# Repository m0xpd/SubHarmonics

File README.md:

# SubHarmonics 

'SubHarmonics' is a Eurorack module which generates two squarewaves ('A' and 'B') which are sub-harmonics of another signal, 'X'.

The signal X is either  
i) generated by the module's internal Voltage Controlled Oscillator  
or  
ii) is derived from an external signal applied to the module's 'Ext X In' input.

The sub-harmonics are generated by hardware dividers, which divide the frequency of X by integer divisors (m, n) of 2, 4, 6, 8, 10, 12, 14, 16 or 18,
giving the unit a range of a little over four octaves (18 ≈ 2 <sup> 4.17 </sup> ). 

These divisors (m := f <sub> x </sub> / f <sub> A </sub>, n := f <sub> x </sub> / f <sub> B </sub>) are voltage controlled - they can be set by potentiometers or by control voltages applied from external sources.

It is seen that the signals A and B are themselves related in frequency by 'the ratio of two small integers' (m/n). So, in addition to each being 
sub-harmonics of X, the ratio between A and B often falls at a musically useful interval; 
<p align="center">
'SubHarmonics' generates harmony as well as bass.
</p>

Other applications of 'SubHarmonics' in Clock Division and Rhythm Generation are described [here.](https://github.com/m0xpd/SubHarmonics/blob/main/Applications/ClockDivision_and_RhythmGeneration.md)

### Internal Modulators

SubHarmonics includes a pair of internal modulators, which combine the A and B signals together (through an OR and an Exclusive OR operation) to
exploit and develop the harmonic relationship between A and B into a richer sound. The OR modulation is equivalent (for these signals A, B) to simple
amplitude modulation, as performed by (e.g.) an AND gate, whilst the Exclusive OR modulation implements the balanced modulation of A with B (as in a 
'ring modulator'). I described the equivalence of OR and AND gates as modulators for the special class of 'antipalindromic' inputs (such as the present 
A and B signals) at tedious length [here.](http://m0xpd.blogspot.com/2023/03/logic-gates-and-modulation-curiosity.html)

The two different modulation results are combined in a voltage-controlled crossfader circuit (controlled by a potentiometer or an external CV input) 
to give a single output which offers a choice OR A MIX of the modulation types at the 'Mod Mix' output.

An introductory video, demonstrating SubHarmonics' features, is available [here](https://youtu.be/j_IT1Ucp6_4)

### Setup

There are two presets that need adjustment on completion of the module to setup for use. Both are located on the topside of the Main Board.

TR2 (a multi-turn 1k preset) controls the 1V/Octave tracking. It should be set by connecting the module to a reliable source of pitch CV signals and monitoring the outputs. I use octave outputs from a BeatStep Pro (you can use a keyboard with CV pitch outputs or simply a known voltage source) and listen to the pitch change. I find it easy to tune octaves by ear but, if you are uncertain, use a tuner or frequency counter.

TR1 (a single turn 100k preset) controls the balance of the modulation mix crossfader. To set it properly requires access to an oscilloscope to see the 'Mod Mix' output waveform. If you have no access to a 'scope, set TR1 to about 60kΩ.

If you do have a 'scope, set the divisors to m=2, n=6 (using the front panel controls) and the frequency to an arbitrary value (around 300Hz). View the 'A' and 'Mod Mix' outputs on the 'scope. Adjust TR1 until you see these waveforms when you put the Mix control at extreme ends of its travel (or, equivalently, apply 0V or 5V CV signals to the Mix input):

(the yellow trace is the 'A' output, which stays the same in this setup process and is included only as a 'reference', the blue trace is the 'Mod Mix' output, which will change when you adjust TR1)  

[If you do not see this waveform on the ModMix output with these settings, it may be due to the phase relationship between the dividers - if this is the case, change the value of 'n' using the potentiometer all the way up to 18 and back to 6 and see if the phase is re-aligned. This is perfectly normal and is not a fault - there is another 'mode' of the system in the m=2, n=6 configuration to that illustrated above.]

Note that the 'Mod Mix' output is inverted (it runs 0 to approx -4V); there wasn't a spare op-amp stage to restore polarity after the crossfader. 
This doesn't matter in ordinary applications; the ear is insensitive to the inversion and it will sound the same! There are, however, some implications of this inversion which are important to the 'time-domain' applications discussed [here.](https://github.com/m0xpd/SubHarmonics/blob/main/Applications/ClockDivision_and_RhythmGeneration.md)

### Miscellaneous Details

The sub-harmonic generation and all signal processing is performed in hardware. 

A small (PIC) microcontroller is used to read the potentiometers and CV inputs and set the dividers. 

Details of the two PCBs and front panel are provided in the [Hardware](https://github.com/m0xpd/SubHarmonics/tree/main/Hardware) folder. Code for 
the 16F676 PIC is presented in the [Controller](https://github.com/m0xpd/SubHarmonics/tree/main/Controller) folder.

SubHarmonics is:  
12HP wide,   
requires 38mm behind the front panel (with the power header fitted) and  
draws 13.5mA from the 12V rail and 5mA from the -12V rail.  

The design is published under a Creative Commons CC BY-SA 4.0 [License](https://github.com/m0xpd/SubHarmonics/blob/main/LICENSE.txt).

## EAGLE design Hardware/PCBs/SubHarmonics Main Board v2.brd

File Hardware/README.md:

# Hardware
This folder contains hardware descriptions of the 'SubHarmonics' module.

The information is presented as EAGLE 'sch' and 'brd' files for the two PCBs (in the [PCBs folder](https://github.com/m0xpd/SubHarmonics/tree/main/Hardware/PCBs) ) and as a small Kicad project for the front panel (in
the FrontPanel folder).

SubHarmonics is implemented in two modules, each of which has its own PCB. There is a Main Board, hosting the majority of the electronics and
a Control Board, which contains all the front panel components including the division indicator LEDs and associated decoders.

## Main Board Description

The Main Board schematic is available [here](https://github.com/m0xpd/SubHarmonics/blob/main/Hardware/SubHarmonics%20Main%20Board%20Schematic%20v2.png) (or by clicking on the graphic below)

The VCO was inspired by the ['Shapes VCO' design by Moritz Klein](https://www.youtube.com/watch?v=QBatvo8bCa4), subsequently used in his VCO for the [Erica Synths Edu DIY VCO](https://www.ericasynths.lv/shop/diy-kits-1/edu-diy-vco/). Since developing 'SubHarmonics', I have learned that the core of the 40106 VCO was not a Klein original, but had been proposed earlier by Mark Shaner (a.k.a. "Synthmonger"), who published the idea [here](https://electro-music.com/forum/topic-28799.html) back in 2008.

The output of this 'Shaner' 40106 VCO - or the input from an external 'X' source - is applied to the 'Divider_In' input of the SubHarmonic Dividers, the input stages of which produce a 0 : 5V pulse at node 'X' on the schematic. There is a detailed description of the derivation of this pulse signal, including
discussion of options to set shared emitter resistor R19 to either maximise input sensitivity or enable a degree of noise immunity, [here.](https://github.com/m0xpd/SubHarmonics/blob/main/Hardware/Graphics/Input%20Stage%20Switching%20Behaviour.md) 

The system was designed around 'available materials' I found lying around my bench - in this case, mainly CD4000-series CMOS logic devices. 

The divisions in each of the two channels are achieved by a CD4015 (Decade counter) and a CD4051 (Analog Mux/Demux) in conventional 
configuration. The divisor is set by a PIC microcontroller, which reads a potentiometer or a CV input signal and decodes the voltage (0-5V) into 
one-of-8 settings for the dividers.

A further divide-by-2 stage, implemented in a CD4013 (D-type SR flip-flop) applied to the outputs of the dividers adds another octave of division 
(necessary to implement the m=2 setting on the A channel).

The outputs of the dividers, A and B (and their complements, not_A and not_B) are fed to two modulators, implemented in a quad NOR package (CD4001).

The results of the OR and XOR operations are mixed in a voltage-controlled crossfader, implemented in half an LM13700.

The [schematic](https://github.com/m0xpd/SubHarmonics/blob/main/Hardware/SubHarmonics%20Main%20Board%20Schematic%20v2.png) and [BoM](https://github.com/m0xpd/SubHarmonics/blob/main/Hardware/PCBs/SubHarmonics%20Main%20Board%20BoM%20v2.txt) show LM324 quad op-amps. These work fine in this application, but you can substitute the ubiquitous TL074 if you prefer. 

The Main Board includes an In-Circuit Serial Programming (ICSP) interface (JP1) to facilitate programming the PIC.

There is a [.sch](https://github.com/m0xpd/SubHarmonics/blob/main/Hardware/PCBs/SubHarmonics%20Main%20Board%20v2.sch) file, a [.brd](https://github.com/m0xpd/SubHarmonics/blob/main/Hardware/PCBs/SubHarmonics%20Main%20Board%20v2.brd) file and a [BoM](https://github.com/m0xpd/SubHarmonics/blob/main/Hardware/PCBs/SubHarmonics%20Main%20Board%20BoM%20v2.txt) for the Main Board in EAGLE format in the [PCBs folder](https://github.com/m0xpd/SubHarmonics/tree/main/Hardware/PCBs).

## Control Board Description

The Control Board schematic is available [here](https://github.com/m0xpd/SubHarmonics/blob/main/Hardware/Control%20Board%20Schematic.png) (or by clicking on the graphic below)

In addition to controls, inputs and outputs, the Control Board hosts the division indicator LEDs and decoders to control these (which again use 
CD4051 analog demuxers).

As well as to CV inputs for Pitch and FM, there are CV inputs for the divisors m and n and for the modulation mix. These last three are designed 
to operate over a range of 0 to 5V, but are protected such that voltages outside these limits will cause no damage.

A 0V input on the modulation mix CV input gives the XOR modulation and a 5V input gives the OR modulation (which is spectrally richer, as it includes the
harmonics of A and B as well as the sum and difference harmonics). An intermediate control voltage gives a mix of both modulation types.

There is a [.sch](https://github.com/m0xpd/SubHarmonics/blob/main/Hardware/PCBs/SubHarmonics%20Control%20Board%20v1.sch) file, a [.brd](https://github.com/m0xpd/SubHarmonics/blob/main/Hardware/PCBs/SubHarmonics%20Control%20Board%20v1.brd) file and a [BoM](https://github.com/m0xpd/SubHarmonics/blob/main/Hardware/PCBs/SubHarmonics%20Control%20Board%20v1%20BoM.txt) for the Control Board in EAGLE format in the [PCBs folder.](https://github.com/m0xpd/SubHarmonics/tree/main/Hardware/PCBs)

The Main and Control boards are joined by two 20-way 0.1 inch pitch headers. These have been specified with electrical redundancy (several pins are 
unused) to provide mechanical stability and security in assembling the module.

The completed PCBs are seen in the photo below, which shows the Main Board from both sides and the Control Board from the 'top' side (the front panel 
components all are mounted on the 'bottom' side).

## Front Panel

A simple Kicad project defining a Front Panel for the module is available in the [FrontPanel folder.](https://github.com/m0xpd/SubHarmonics/tree/main/Hardware/FrontPanel)

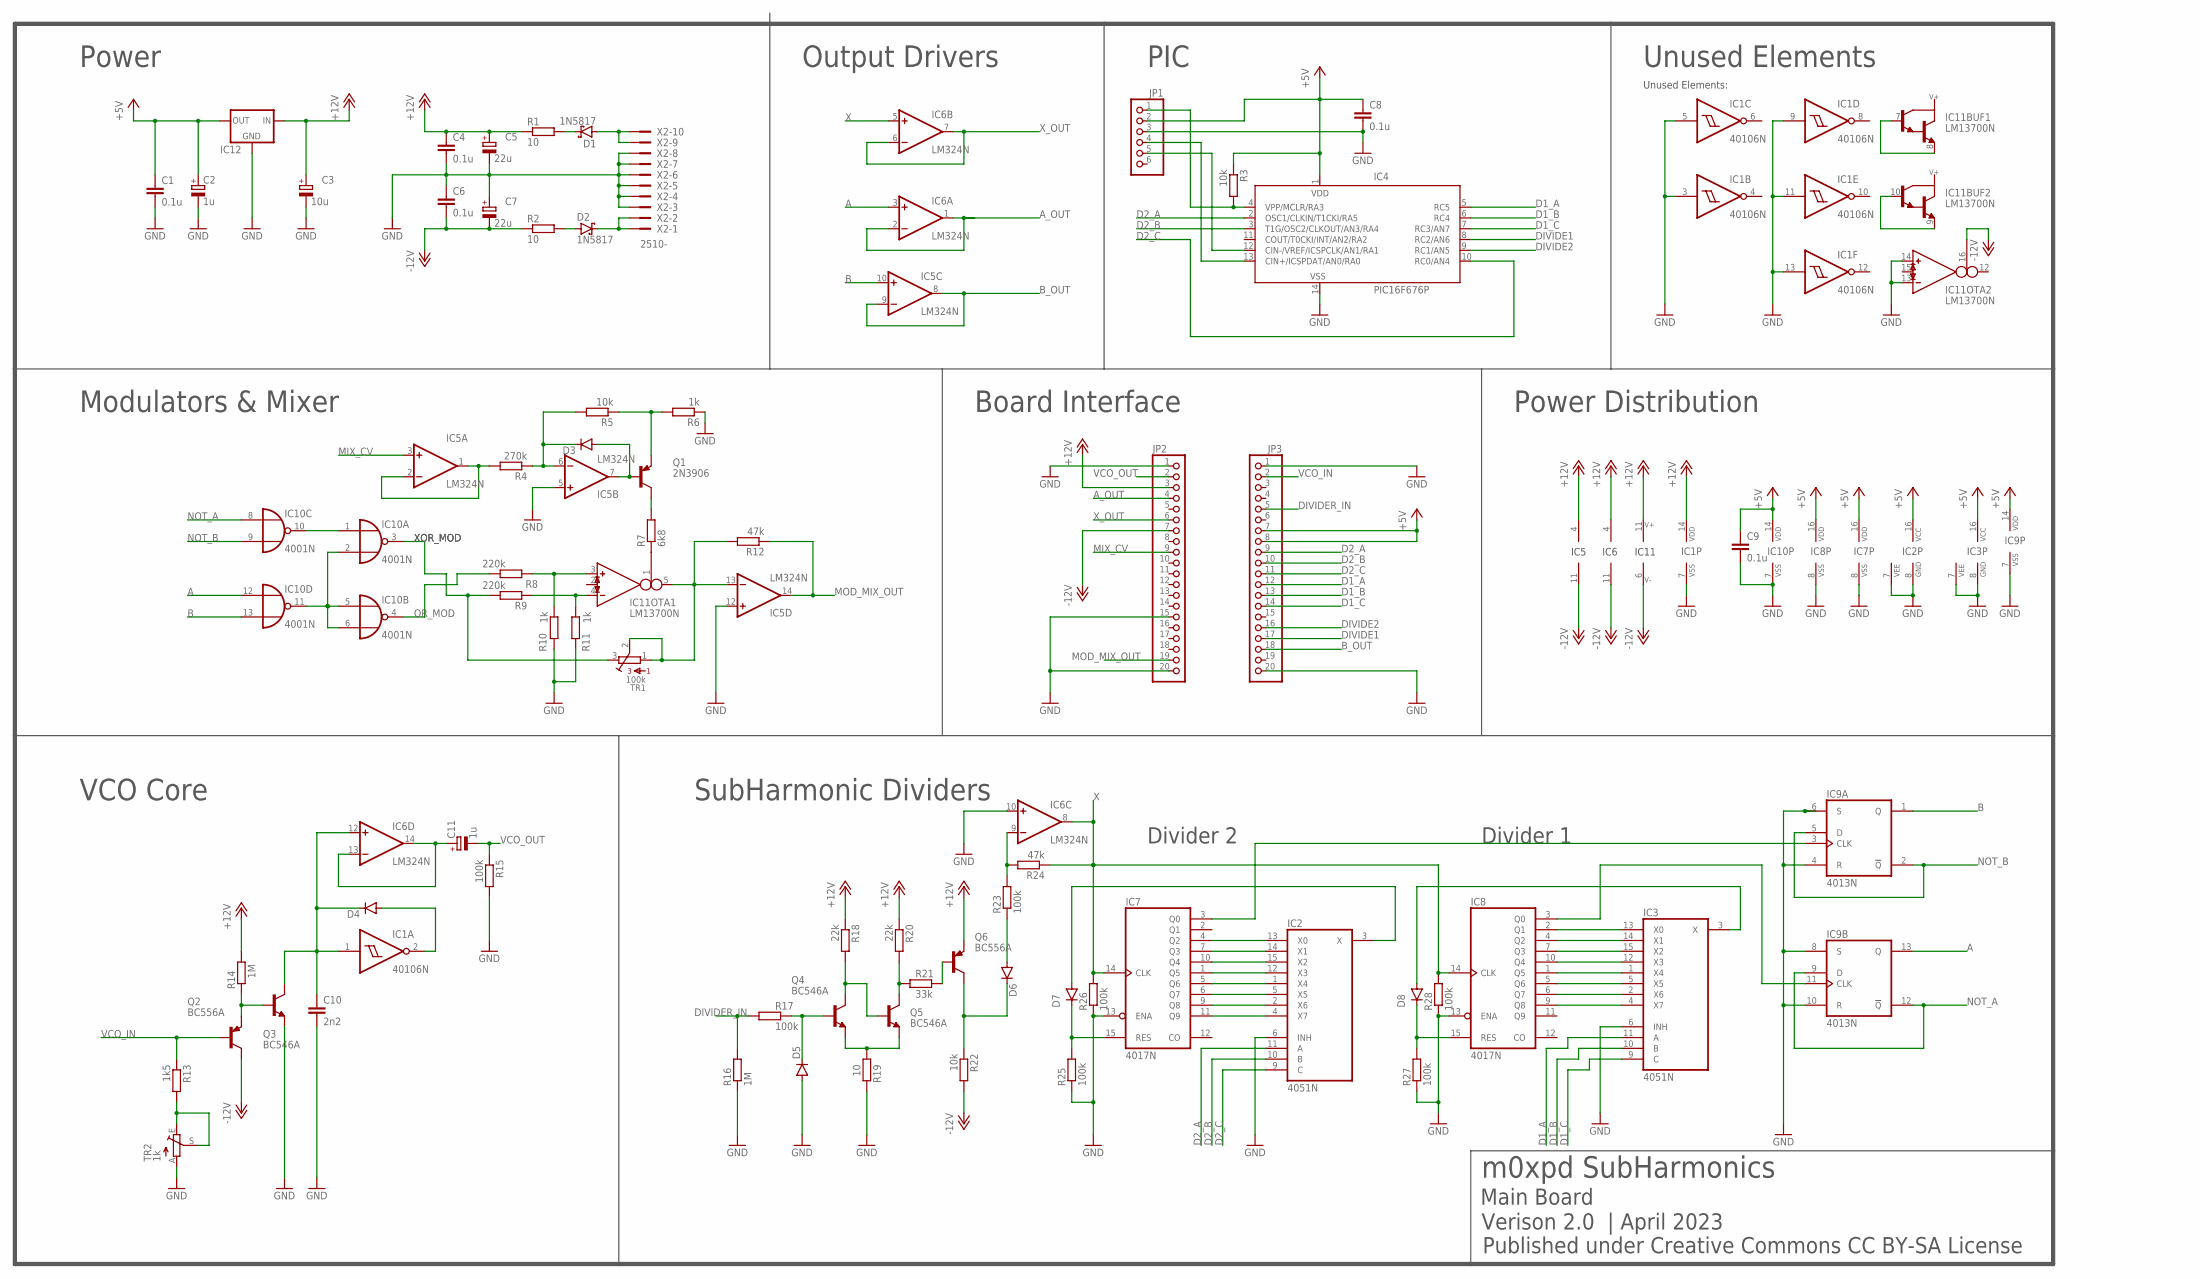
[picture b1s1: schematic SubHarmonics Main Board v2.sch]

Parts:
C1, C4, C6, C8, C9: 0.1u; C050-025X075
C2, C11: 1u; E2,5-5
C3: 10u; E2,5-5
C5, C7: 22u; E2,5-5
C10: 2n2; C050-030X075
D1, D2: 1N5817; DO35-7
D3, D4, D5, D6, D7, D8: 1N4148DO35-7; DO35-7
IC1: 40106N; DIL14
IC2, IC3: 4051N; DIL16
IC4: PIC16F676P; DIL14
IC5, IC6: LM324N; DIL14
IC7, IC8: 4017N; DIL16
IC9: 4013N; DIL14
IC10: 4001N; DIL14
IC11: LM13700N; DIL16
IC12: 78LXX
JP1: PINHD-1X6; 1X06
JP2, JP3: PINHD-1X20; 1X20
Q1: 2N3906; TO92
Q2, Q6: BC556A; TO92-EBC
Q3, Q4, Q5: BC546A; TO92-EBC
R1, R2, R19: 10; 0204/7
R3, R5, R22: 10k; 0204/7
R4: 270k; 0204/7
R6, R10, R11: 1k; 0204/7
R7: 6k8; 0204/7
R8, R9: 220k; 0204/7
R12, R24: 47k; 0204/7
R13: 1k5; 0204/7
R14, R16: 1M; 0204/7
R15, R17, R23, R25, R26, R27, R28: 100k; 0204/7
R18, R20: 22k; 0204/7
R21: 33k; 0204/7
TR1: 100k; BOURNS_3362P_TRIMMER
TR2: 1k; B64Y
X2: 2510-; PAK100/2500-10

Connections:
+5V: C1.1, C2.+, C8.1, C9.1, IC2.16 (VCC), IC3.16 (VCC), IC4.1 (VDD), IC7.16 (VDD), IC8.16 (VDD), IC9.14 (VDD), IC10.14 (VDD), IC12.OUT, JP1.2, JP3.7, JP3.8, R3.1
+12V: C3.+, C4.1, C5.+, IC1.14 (VDD), IC5.4 (V+), IC6.4 (V+), IC11.11 (V+), IC12.IN, JP2.3, Q6.E, R1.1, R14.2, R18.1, R20.1
-12V: C6.2, C7.-, IC5.11 (V-), IC6.11 (V-), IC11.6 (V-), IC11.16 (I_BIAS), JP2.7, Q2.C, R2.1, R22.2
A: IC6.3 (+IN), IC9.13 (Q), IC10.12 (I0)
A_OUT: IC6.1 (OUT), IC6.2 (-IN), JP2.4
B: IC5.10 (+IN), IC9.1 (Q), IC10.13 (I1)
B_OUT: IC5.8 (OUT), IC5.9 (-IN), JP3.18
D1_A: IC3.11 (A), IC4.5 (RC5), JP3.12
D1_B: IC3.10 (B), IC4.6 (RC4), JP3.13
D1_C: IC3.9 (C), IC4.7 (RC3/AN7), JP3.14
D2_A: IC2.11 (A), IC4.2 (OSC1/CLKIN/T1CKI/RA5), JP3.9
D2_B: IC2.10 (B), IC4.3 (T1G/OSC2/CLKOUT/AN3/RA4), JP3.10
D2_C: IC2.9 (C), IC4.10 (RC0/AN4), JP3.11
DIVIDE1: IC4.8 (RC2/AN6), JP3.17
DIVIDE2: IC4.9 (RC1/AN5), JP3.16
DIVIDER_IN: JP3.5, R16.2, R17.1
GND: C1.2, C2.-, C3.-, C4.2, C5.-, C6.1, C7.+, C8.2, C9.2, C10.2, D5.A, IC1.3 (I), IC1.5 (I), IC1.7 (VSS), IC1.9 (I), IC1.11 (I), IC1.13 (I), IC2.6 (INH), IC2.7 (VEE), IC2.8 (GND), IC3.6 (INH), IC3.7 (VEE), IC3.8 (GND), IC4.14 (VSS), IC5.5 (+IN), IC5.12 (+IN), IC6.10 (+IN), IC7.8 (VSS), IC7.13 (ENA), IC8.8 (VSS), IC8.13 (ENA), IC9.4 (R), IC9.6 (S), IC9.7 (VSS), IC9.8 (S), IC9.10 (R), IC10.7 (VSS), IC11.13 (IN_N), IC11.14 (IN_P), IC12.GND, JP1.3, JP2.1, JP2.15, JP2.20, JP3.1, JP3.20, Q3.E, R6.1, R10.2, R11.2, R15.2, R16.1, R19.2, R25.1, R26.1, R27.1, R28.1, TR2.A, X2.3, X2.4, X2.5, X2.6, X2.7, X2.8
MIX_CV: IC5.3 (+IN), JP2.9
MOD_MIX_OUT: IC5.14 (OUT), JP2.19, R12.1
unnamed: IC2.2 (X6), IC7.9 (Q8)
unnamed: IC5.1 (OUT), IC5.2 (-IN), R4.2
unnamed: D7.C, IC7.15 (RES), R25.2
unnamed: D7.A, IC2.3 (X)
unnamed: IC2.13 (X0), IC7.4 (Q2)
unnamed: IC2.14 (X1), IC7.7 (Q3)
unnamed: IC2.15 (X2), IC7.10 (Q4)
unnamed: IC2.12 (X3), IC7.1 (Q5)
unnamed: IC2.1 (X4), IC7.5 (Q6)
unnamed: IC2.5 (X5), IC7.6 (Q7)
unnamed: IC2.4 (X7), IC7.11 (Q9)
unnamed: IC11.3 (IN_P), R8.1, R10.1
unnamed: D1.A, X2.9, X2.10
unnamed: D1.C, R1.2
unnamed: IC4.4 (VPP/MCLR/RA3), JP1.1, R3.2
unnamed: D8.C, IC8.15 (RES), R27.2
unnamed: D8.A, IC3.3 (X)
unnamed: IC11.7 (B), IC11.8 (E)
unnamed: IC3.14 (X1), IC8.4 (Q2)
unnamed: IC3.15 (X2), IC8.7 (Q3)
unnamed: IC3.12 (X3), IC8.10 (Q4)
unnamed: IC3.1 (X4), IC8.1 (Q5)
unnamed: IC3.5 (X5), IC8.5 (Q6)
unnamed: IC3.2 (X6), IC8.6 (Q7)
unnamed: IC3.4 (X7), IC8.9 (Q8)
unnamed: IC11.4 (IN_N), R9.1, R11.1
unnamed: D2.A, R2.2
unnamed: D2.C, X2.1, X2.2
unnamed: IC11.9 (E), IC11.10 (B)
unnamed: IC11.1 (I_BIAS), R7.1
unnamed: IC4.13 (CIN+/ICSPDAT/AN0/RA0), JP1.4
unnamed: IC4.12 (CIN-/VREF/ICSPCLK/AN1/RA1), JP1.5
unnamed: IC3.13 (X0), IC8.2 (Q1)
unnamed: IC8.3 (Q0), IC9.11 (CLK)
unnamed: IC7.3 (Q0), IC9.3 (CLK)
unnamed: R13.2, TR2.E, TR2.S
unnamed: D6.C, Q6.C, R22.1
unnamed: D6.A, R23.1
unnamed: D4.A, IC1.2 (O)
unnamed: C10.1, D4.C, IC1.1 (I), IC6.12 (+IN), Q3.C
unnamed: Q2.E, Q3.B, R14.1
unnamed: IC6.9 (-IN), R23.2, R24.2
unnamed: C11.+, IC6.13 (-IN), IC6.14 (OUT)
unnamed: Q4.E, Q5.E, R19.1
unnamed: IC10.1 (I0), IC10.10 (O)
unnamed: IC10.2 (I1), IC10.5 (I0), IC10.6 (I1), IC10.11 (O)
unnamed: D5.C, Q4.B, R17.2
unnamed: Q1.1 (C), R7.2
unnamed: D3.C, IC5.6 (-IN), R4.1, R5.2
unnamed: Q4.C, Q5.B, R18.2
unnamed: Q5.C, R20.2, R21.1
unnamed: D3.A, IC5.7 (OUT), Q1.2 (B)
unnamed: Q1.3 (E), R5.1, R6.2
unnamed: Q6.B, R21.2
unnamed: IC5.13 (-IN), IC11.5 (OUT), R12.2, TR1.1, TR1.2
NOT_A: IC9.9 (D), IC9.12 (!Q), IC10.8 (I0)
NOT_B: IC9.2 (!Q), IC9.5 (D), IC10.9 (I1)
OR_MOD: IC10.4 (O), R8.2
VCO_IN: JP3.2, Q2.B, R13.1
VCO_OUT: C11.-, JP2.2, R15.1
X: IC6.5 (+IN), IC6.8 (OUT), IC7.14 (CLK), IC8.14 (CLK), R24.1, R26.2, R28.2
XOR_MOD: IC10.3 (O), R9.2, TR1.3
X_OUT: IC6.6 (-IN), IC6.7 (OUT), JP2.6

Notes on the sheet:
Unused Elements:
Divider 1
Divider 2
m0xpd SubHarmonics
Main Board
Verison 2.0 | April 2023
Published under Creative Commons CC BY-SA License
VCO Core
SubHarmonic Dividers
Modulators & Mixer
Power
Output Drivers
PIC
Unused Elements
Power Distribution
Board Interface
IC5
IC6
IC11

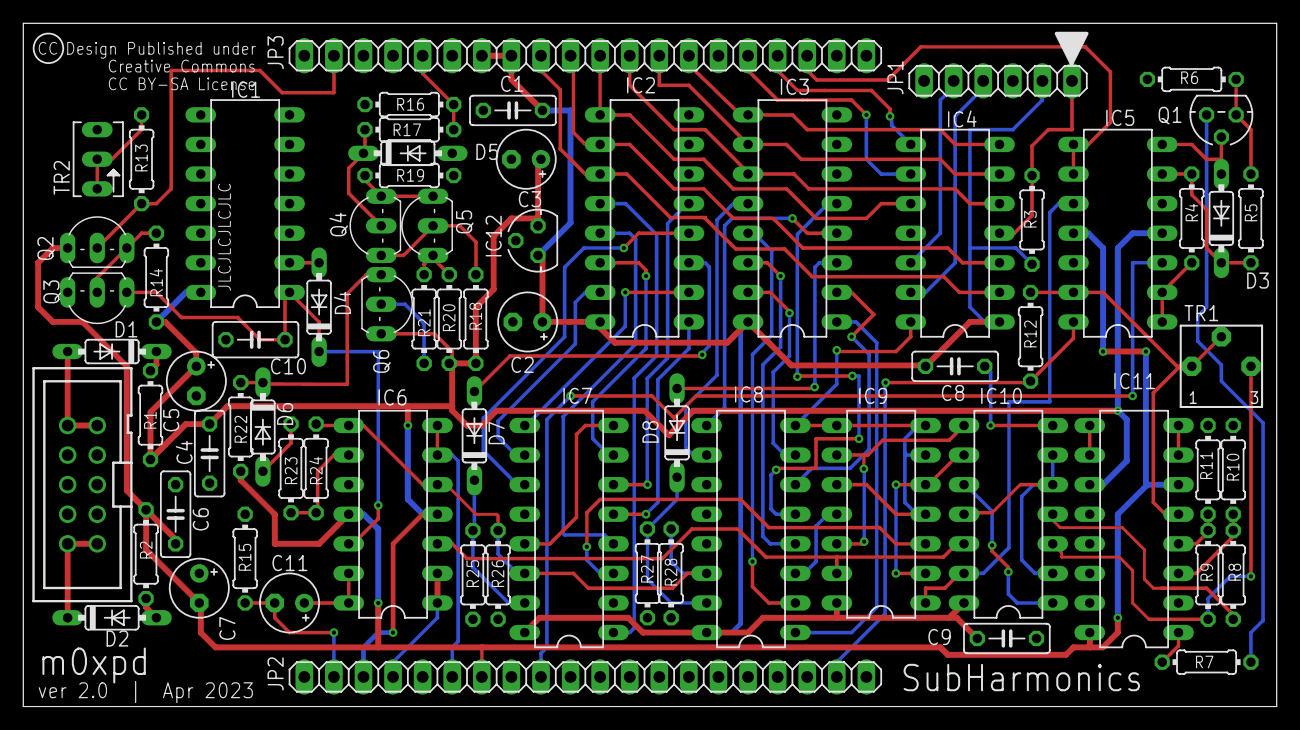
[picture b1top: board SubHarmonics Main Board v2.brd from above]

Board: 2 copper layers, 107.6 x 58.7 mm, 71 parts (0 on the bottom side), 82 nets.

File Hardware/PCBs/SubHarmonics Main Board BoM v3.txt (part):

Partlist exported from /Users/pauldarlington/Documents/EAGLE/projects/Harmonic Division Oscillator/SubHarmonics Main Board v3.sch at 22/10/2023 06:24

Part Value        Device                Package              Description                                    MF        MPN           OC_FARNELL OC_NEWARK POPULARITY SPICEPREFIX
C1   0.1u         C-EU050-025X075       C050-025X075         CAPACITOR, European symbol                                                                  29         C          
C2   1u           CPOL-EUE2.5-5         E2,5-5               POLARIZED CAPACITOR, European symbol                                                        16         C          
C3   10u          CPOL-EUE2.5-5         E2,5-5               POLARIZED CAPACITOR, European symbol                                                        16         C          
C4   0.1u         C-EU050-025X075       C050-025X075         CAPACITOR, European symbol                                                                  29         C          
C5   22u          CPOL-EUE2.5-5         E2,5-5               POLARIZED CAPACITOR, European symbol                                                        16         C          
C6   0.1u         C-EU050-025X075       C050-025X075         CAPACITOR, European symbol                                                                  29         C          
C7   22u          CPOL-EUE2.5-5         E2,5-5               POLARIZED CAPACITOR, European symbol                                                        16         C          
C8   0.1u         C-EU050-025X075       C050-025X075         CAPACITOR, European symbol                                                                  29         C          
C9   0.1u         C-EU050-025X075       C050-025X075         CAPACITOR, European symbol                                                                  29         C          
C10  2n2          C-EU050-030X075       C050-030X075         CAPACITOR, European symbol                                                                  9          C          
C11  1u           CPOL-EUE2.5-5         E2,5-5               POLARIZED CAPACITOR, European symbol                                                        16         C          
D1   1N5817       SCHOTTKY-DIODEDO35-7  DO35-7               Schottky Diode                                                                              3                     
D2   1N5817       SCHOTTKY-DIODEDO35-7  DO35-7               Schottky Diode                                                                              3                     
D3   1N4148DO35-7 1N4148DO35-7          DO35-7               DIODE                                                                                       58                    
D4   1N4148DO35-7 1N4148DO35-7          DO35-7               DIODE                                                                                       58                    
D5   1N4148DO35-7 1N4148DO35-7          DO35-7               DIODE                                                                                       58                    
D6   1N4148DO35-7 1N4148DO35-7          DO35-7               DIODE                                                                                       58                    
D7   1N4148DO35-7 1N4148DO35-7          DO35-7               DIODE                                                                                       58                    
D8   1N4148DO35-7 1N4148DO35-7          DO35-7               DIODE                                                                                       58                    
IC1  40106N       40106N                DIL14                Hex SCHMITT TRIGGER                                                                         4                     
IC2  4051N        4051N                 DIL16                8-channel ANALOG MULTIPLEXER                                                                15                    
IC3  4051N        4051N                 DIL16                8-channel ANALOG MULTIPLEXER                                                                15                    
IC4  PIC16F676P   PIC16F676P            DIL14                14-Pin, Flash-Based 8-Bit CMOS Microcontroller MICROCHIP PIC16F676-I/P 9760512    54K2829   0                     
IC5  LM324N       LM324N                DIL14                OP AMP                                                                                      9                     
IC6  LM324N       LM324N                DIL14                OP AMP                                                                                      9                     
IC7  4017N        4017N                 DIL16                COUNTER/DIVIDER                                                                             2                     
IC8  4017N        4017N                 DIL16                COUNTER/DIVIDER                                                                             2                     
IC9  4013N        4013N                 DIL14                Dual D FLIP FLOP, set/reset                                                                 4                     
IC10 4001N        4001N                 DIL14                Quad 2-input NOR                                                                            1                     
IC11 LM13700N     LM13700N              DIL16                Dual OTA with buffers                                                                                             
IC12              78LXX                 78LXX                VOLTAGE REGULATOR                                                                           6                     
JP1               PINHD-1X6             1X06                 PIN HEADER                                                                                  79                    
JP2               PINHD-1X20            1X20                 PIN HEADER                                                                                  6                     
JP3               PINHD-1X20            1X20                 PIN HEADER                                                                                  6                     
Q1   2N3906       2N3906                TO92                 PNP Transistor                                                                              11                    
Q2   BC556A       BC556A                TO92-EBC             PNP Transistror                                                                             0                     
Q3   BC546A       BC546A                TO92-EBC             NPN Transistor                                                                              0                     
Q4   BC546A       BC546A                TO92-EBC             NPN Transistor                                                                              0                     
Q5   BC546A       BC546A                TO92-EBC             NPN Transistor                                                                              0                     
Q6   BC556A       BC556                 TO92-EBC             PNP Transistror                                                                             2                     
R1   10           R-EU_0204/7           0204/7               RESISTOR, European symbol                                                                   79         R          
R2   10           R-EU_0204/7           0204/7               RESISTOR, European symbol                                                                   79         R          
R3   10k          R-EU_0204/7           0204/7               RESISTOR, European symbol                                                                   79         R          
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
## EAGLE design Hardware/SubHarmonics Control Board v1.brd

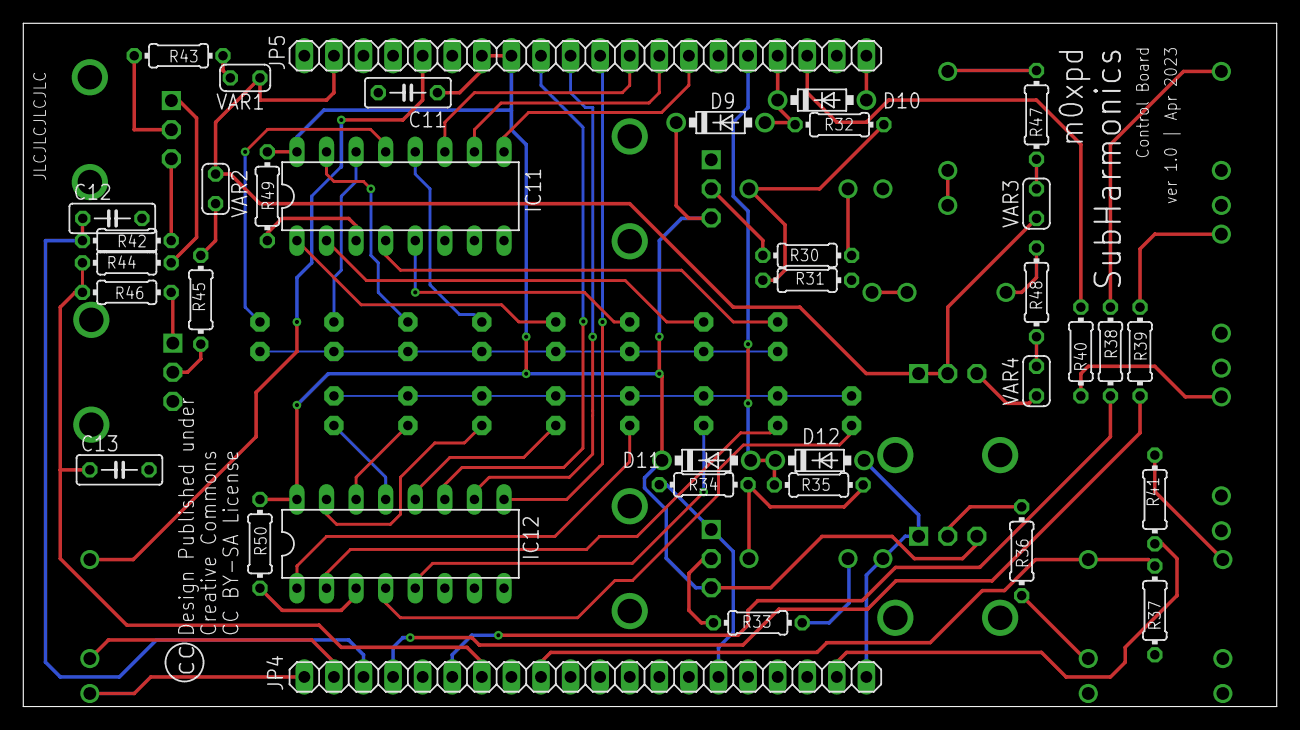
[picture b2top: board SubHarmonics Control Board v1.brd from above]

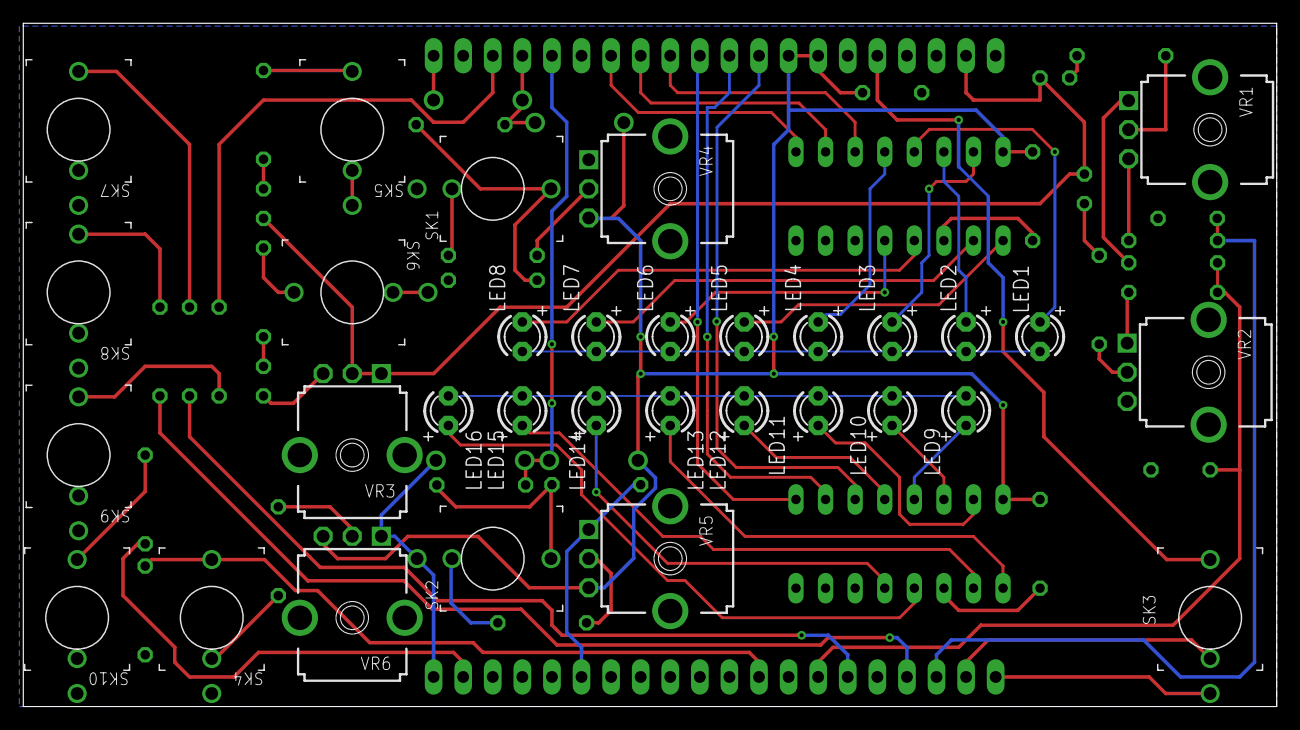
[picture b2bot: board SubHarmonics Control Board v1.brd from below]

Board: 2 copper layers, 107.6 x 58.7 mm, 68 parts (32 on the bottom side), 62 nets.

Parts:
C11, C12, C13: 0.1u; C050-025X075
D9, D10, D11, D12: 1N5817-T; DO41-7.6
IC11, IC12: 4051N; DIL16
JP4, JP5: 1X20
LED1, LED2, LED3, LED4, LED5, LED6, LED7, LED8, LED9, LED10, LED11, LED12, LED13, LED14, LED15, LED16: LED3MM
R30, R33, R36: 1k; 0204/7
R31, R34, R37: 220k; 0204/7
R32, R35: 10k; 0204/7
R38, R39, R40, R41: 470; 0204/7
R42, R43, R46, R47, R48: 100k; 0204/7
R44: 33k; 0204/7
R45: 1M; 0204/7
R49, R50: 2k2; 0204/7
SK1, SK2, SK3, SK4, SK5, SK6, SK7, SK8, SK9, SK10: THONKICONN_JACK; WQP-PJ301M-12_JACK
VAR1, VAR2, VAR3, VAR4: 10k; C025-024X044
VR1, VR2, VR4, VR5, VR6: 100k; 9MM_SNAP-IN_POT
VR3: 1M; 9MM_SNAP-IN_POT

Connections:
+5V: C11.1, D9.C, D11.C, IC11.16, IC12.16, JP5.7, JP5.8, R49.2, R50.2, VR4.3, VR5.3, VR6.3
+12V: C12.1, JP4.3, R42.1
-12V: C13.1, JP4.7, R44.2, R46.1
A_OUT: JP4.4, R39.1
B_OUT: JP5.18, R40.1
D1_A: IC11.11, JP5.12
D1_B: IC11.10, JP5.13
D1_C: IC11.9, JP5.14
D2_A: IC12.11, JP5.9
D2_B: IC12.10, JP5.10
D2_C: IC12.9, JP5.11
DIVIDE1: D9.A, D10.C, JP5.17, R32.2
DIVIDE2: D11.A, D12.C, JP5.16, R35.2
DIVIDER_IN: JP5.5, SK3.P$1_TIP
GND: C11.2, C12.2, C13.2, D10.A, D12.A, IC11.6, IC11.7, IC11.8, IC12.6, IC12.7, IC12.8, JP4.1, JP4.15, JP4.20, JP5.1, JP5.20, LED1.K, LED2.K, LED3.K, LED4.K, LED5.K, LED6.K, LED7.K, LED8.K, LED9.K, LED10.K, LED11.K, LED12.K, LED13.K, LED14.K, LED15.K, LED16.K, R31.2, R34.2, R37.2, SK1.P$3_SLEEVE, SK2.P$3_SLEEVE, SK3.P$3_SLEEVE, SK4.P$3_SLEEVE, SK5.P$2_SWITCH, SK5.P$3_SLEEVE, SK6.P$2_SWITCH, SK6.P$3_SLEEVE, SK7.P$3_SLEEVE, SK8.P$3_SLEEVE, SK9.P$3_SLEEVE, SK10.P$3_SLEEVE, VR2.3, VR4.1, VR5.1, VR6.1
MIX_CV: JP4.9, R37.1, SK4.P$1_TIP
MOD_MIX_OUT: JP4.19, R41.1
unnamed: R38.2, SK7.P$1_TIP
unnamed: R39.2, SK8.P$1_TIP
unnamed: R40.2, SK9.P$1_TIP
unnamed: R41.2, SK10.P$1_TIP
unnamed: R30.1, SK1.P$2_SWITCH
unnamed: R31.1, R32.1, SK1.P$1_TIP
unnamed: R42.2, VR1.3
unnamed: R44.1, VR1.1
unnamed: R43.1, VR1.2
unnamed: R43.2, VAR1.2
unnamed: R47.2, VAR3.2
unnamed: R47.1, SK5.P$1_TIP
unnamed: R46.2, VR2.1
unnamed: R45.1, VR2.2
unnamed: R45.2, VAR2.2
unnamed: R48.1, SK6.P$1_TIP
unnamed: R48.2, VAR4.2
unnamed: VAR4.1, VR3.3
unnamed: R30.2, VR4.2
unnamed: R33.1, SK2.P$2_SWITCH
unnamed: R34.1, R35.1, SK2.P$1_TIP
unnamed: IC11.13, LED1.A
unnamed: IC11.14, LED2.A
unnamed: IC11.15, LED3.A
unnamed: IC11.12, LED4.A
unnamed: IC11.1, LED5.A
unnamed: IC11.5, LED6.A
unnamed: IC11.2, LED7.A
unnamed: IC11.4, LED8.A
unnamed: IC12.13, LED9.A
unnamed: IC11.3, R49.1
unnamed: IC12.14, LED10.A
unnamed: IC12.15, LED11.A
unnamed: IC12.12, LED12.A
unnamed: IC12.1, LED13.A
unnamed: IC12.5, LED14.A
unnamed: IC12.2, LED15.A
unnamed: IC12.4, LED16.A
unnamed: R33.2, VR5.2
unnamed: IC12.3, R50.1
unnamed: R36.1, SK4.P$2_SWITCH
unnamed: R36.2, VR6.2
VCO_IN: JP5.2, VAR1.1, VAR2.1, VAR3.1, VR3.1, VR3.2
VCO_OUT: JP4.2, SK3.P$2_SWITCH
X_OUT: JP4.6, R38.1

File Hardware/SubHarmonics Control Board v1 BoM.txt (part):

Partlist exported from /Users/pauldarlington/Documents/EAGLE/projects/Harmonic Division Oscillator/SubHarmonics Control Board v1.sch at 04/05/2023 07:58

Part  Value           Device           Package            Description                                       POPULARITY SPICEPREFIX
C11   0.1u            C-EU050-025X075  C050-025X075       CAPACITOR, European symbol                        29         C          
C12   0.1u            C-EU050-025X075  C050-025X075       CAPACITOR, European symbol                        29         C          
C13   0.1u            C-EU050-025X075  C050-025X075       CAPACITOR, European symbol                        29         C          
D9    1N5817-T        1N5817-T         DO41-7.6           1.0A SCHOTTKY BARRIER RECTIFIER                   0                     
D10   1N5817-T        1N5817-T         DO41-7.6           1.0A SCHOTTKY BARRIER RECTIFIER                   0                     
D11   1N5817-T        1N5817-T         DO41-7.6           1.0A SCHOTTKY BARRIER RECTIFIER                   0                     
D12   1N5817-T        1N5817-T         DO41-7.6           1.0A SCHOTTKY BARRIER RECTIFIER                   0                     
IC11  4051N           4051N            DIL16              8-channel ANALOG MULTIPLEXER                      15                    
IC12  4051N           4051N            DIL16              8-channel ANALOG MULTIPLEXER                      15                    
JP4                   PINHD-1X20       1X20               PIN HEADER                                        6                     
JP5                   PINHD-1X20       1X20               PIN HEADER                                        6                     
LED1                  LED3MM           LED3MM             LED                                                                     
LED2                  LED3MM           LED3MM             LED                                                                     
LED3                  LED3MM           LED3MM             LED                                                                     
LED4                  LED3MM           LED3MM             LED                                                                     
LED5                  LED3MM           LED3MM             LED                                                                     
LED6                  LED3MM           LED3MM             LED                                                                     
LED7                  LED3MM           LED3MM             LED                                                                     
LED8                  LED3MM           LED3MM             LED                                                                     
LED9                  LED3MM           LED3MM             LED                                                                     
LED10                 LED3MM           LED3MM             LED                                                                     
LED11                 LED3MM           LED3MM             LED                                                                     
LED12                 LED3MM           LED3MM             LED                                                                     
LED13                 LED3MM           LED3MM             LED                                                                     
LED14                 LED3MM           LED3MM             LED                                                                     
LED15                 LED3MM           LED3MM             LED                                                                     
LED16                 LED3MM           LED3MM             LED                                                                     
R30   1k              R-EU_0204/7      0204/7             RESISTOR, European symbol                         79         R          
R31   220k            R-EU_0204/7      0204/7             RESISTOR, European symbol                         79         R          
R32   10k             R-EU_0204/7      0204/7             RESISTOR, European symbol                         79         R          
R33   1k              R-EU_0204/7      0204/7             RESISTOR, European symbol                         79         R          
R34   220k            R-EU_0204/7      0204/7             RESISTOR, European symbol                         79         R          
R35   10k             R-EU_0204/7      0204/7             RESISTOR, European symbol                         79         R          
R36   1k              R-EU_0204/7      0204/7             RESISTOR, European symbol                         79         R          
R37   220k            R-EU_0204/7      0204/7             RESISTOR, European symbol                         79         R          
R38   470             R-EU_0204/7      0204/7             RESISTOR, European symbol                         79         R          
R39   470             R-EU_0204/7      0204/7             RESISTOR, European symbol                         79         R          
R40   470             R-EU_0204/7      0204/7             RESISTOR, European symbol                         79         R          
R41   470             R-EU_0204/7      0204/7             RESISTOR, European symbol                         79         R          
R42   100k            R-EU_0204/7      0204/7             RESISTOR, European symbol                         79         R          
R43   100k            R-EU_0204/7      0204/7             RESISTOR, European symbol                         79         R          
R44   33k             R-EU_0204/7      0204/7             RESISTOR, European symbol                         79         R          
R45   1M              R-EU_0204/7      0204/7             RESISTOR, European symbol                         79         R          
R46   100k            R-EU_0204/7      0204/7             RESISTOR, European symbol                         79         R          
R47   100k            R-EU_0204/7      0204/7             RESISTOR, European symbol                         79         R          
R48   100k            R-EU_0204/7      0204/7             RESISTOR, European symbol                         79         R          
R49   2k2             R-EU_0204/7      0204/7             RESISTOR, European symbol                         79         R          
R50   2k2             R-EU_0204/7      0204/7             RESISTOR, European symbol                         79         R          
SK1   THONKICONN_JACK THONKICONN_JACK  WQP-PJ301M-12_JACK                                                                         
SK2   THONKICONN_JACK THONKICONN_JACK  WQP-PJ301M-12_JACK                                                                         
SK3   THONKICONN_JACK THONKICONN_JACK  WQP-PJ301M-12_JACK                                                                         
SK4   THONKICONN_JACK THONKICONN_JACK  WQP-PJ301M-12_JACK                                                                         
SK5   THONKICONN_JACK THONKICONN_JACK  WQP-PJ301M-12_JACK                                                                         
SK6   THONKICONN_JACK THONKICONN_JACK  WQP-PJ301M-12_JACK                                                                         
SK7   THONKICONN_JACK THONKICONN_JACK  WQP-PJ301M-12_JACK                                                                         
SK8   THONKICONN_JACK THONKICONN_JACK  WQP-PJ301M-12_JACK                                                                         
SK9   THONKICONN_JACK THONKICONN_JACK  WQP-PJ301M-12_JACK                                                                         
SK10  THONKICONN_JACK THONKICONN_JACK  WQP-PJ301M-12_JACK                                                                         
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

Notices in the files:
Hardware/PCBs/SubHarmonics Main Board v2.brd:
Design Published under
Creative Commons
CC BY-SA License
